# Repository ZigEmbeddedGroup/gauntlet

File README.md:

# Gauntlet

Gauntlet is [MicroZig](https://github.com/ZigEmbeddedGroup/microzig)'s
hardware-in-loop (HIL) testing system.

MicroZig gives users interfaces to program embedded hardware using Zig.
Contributors have to test manually, and both bugs and regressions make it into
the codebase regularly.

One may assume that software emulators would be the next logical step, they're
deterministic and can be run anywhere. This is still a lot of work, either
requires building our own simulators, or depending on others, and it doesn't
fully answer the question, does it actually work on hardware?

With this more ambitious project we put in more work and resources than the
simulator path, but we can truely answer the question of whether something works
on real hardware. The other thing this system will give us is the ability to
test Zig compiler codegen for embedded targets.

## Architecture

The physical structure of the testing system follows the
[Eurocard](https://en.wikipedia.org/wiki/Eurocard_(printed_circuit_board))
format. This is a common mechanical standard which enforces no connector or
signal formats, but means there are different enclosure options, many of which
are rack mountable! It also means we can design different sized versions of the
system.

There are three types of components in the system:

- A main board housing a computer, power supply, and bus control circuitry.
- Individual device-under-test (DUT) boards.
- A backplane which houses the bus. All the boards plug into it.

The power plug for this system will be USB-C as we have members in different
countries with different plugs. We will make use of the standard USB-PD range,
which can deliver 100W of power.

Only one DUT board is active at a time.

## Security Model

Security and convenience are often at odds and it takes good design to bridge
the two.

To kick this good design down the road while safely getting utility ASAP, members
running this system will manually trigger test runs after they have reviewed a
PR.

This design is open-source and anyone is welcome to build their own boards for
their own local testing. Only the results from core team members will be
trusted.

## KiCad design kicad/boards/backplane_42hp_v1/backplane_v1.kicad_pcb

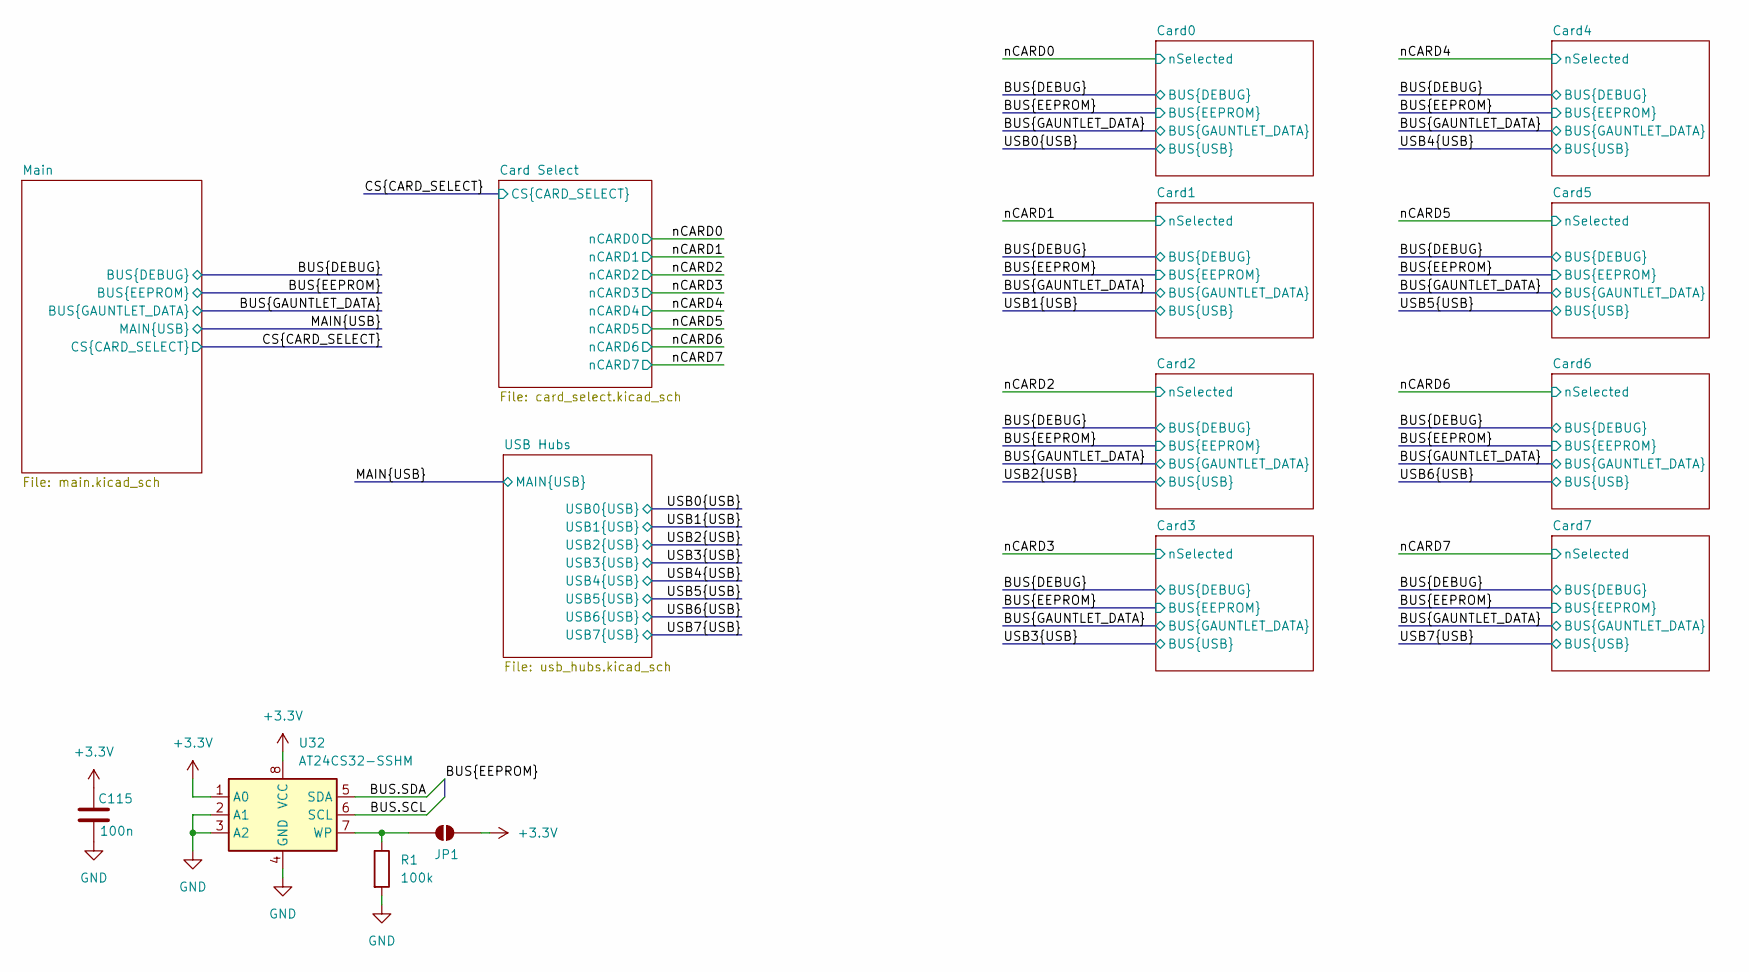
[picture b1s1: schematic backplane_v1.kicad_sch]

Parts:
C115: 100n; C_0603_1608Metric
JP1: SolderJumper_2_Open; SolderJumper-2_P1.3mm_Open_RoundedPad1.0x1.5mm
R1: 100k; R_0402_1005Metric
U32: AT24CS32-SSHM; SOIC-8_3.9x4.9mm_P1.27mm

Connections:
+3.3V: C115.1, JP1.2 (B), U32.1 (A0), U32.8 (VCC); also elsewhere on the board
/BUS.SCL: U32.6 (SCL); also elsewhere on the board
/BUS.SDA: U32.5 (SDA); also elsewhere on the board
GND: C115.2, R1.2, U32.2 (A1), U32.3 (A2), U32.4 (GND); also elsewhere on the board
unnamed: JP1.1 (A), R1.1, U32.7 (WP)
